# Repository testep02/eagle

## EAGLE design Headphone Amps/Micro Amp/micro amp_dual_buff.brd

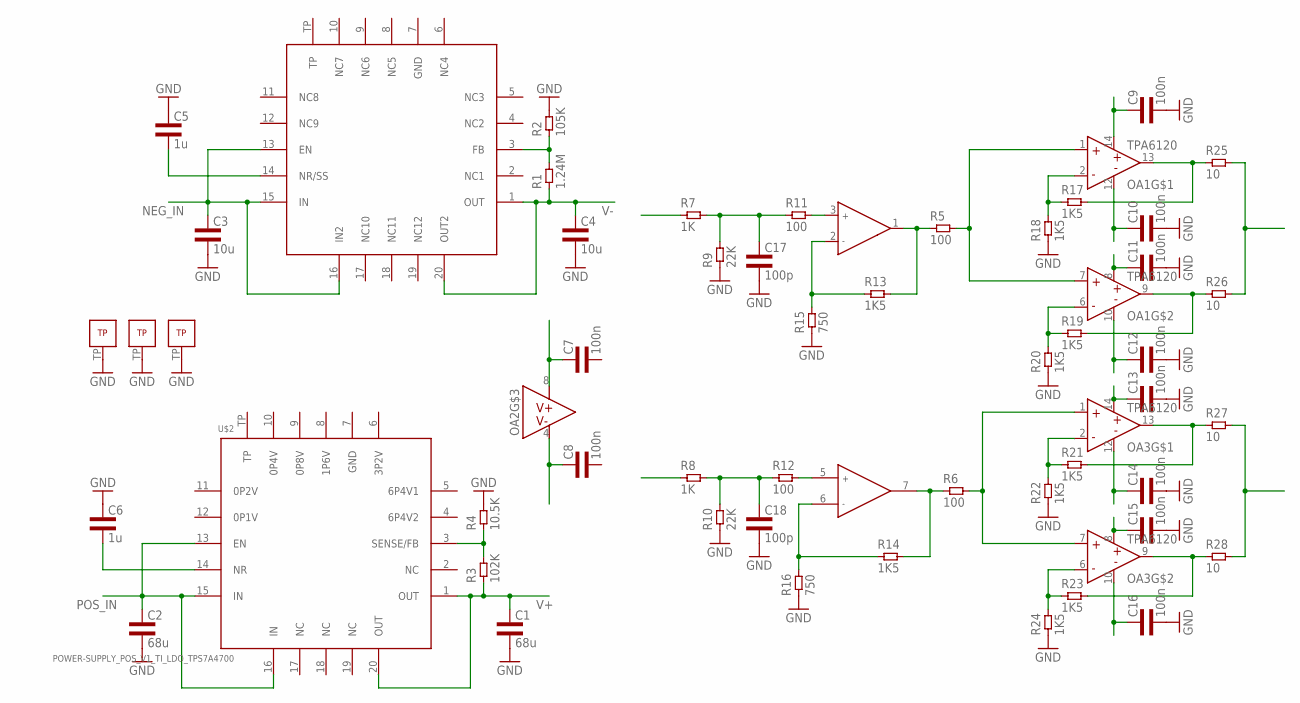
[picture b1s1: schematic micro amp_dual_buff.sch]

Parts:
C1, C2: 68u; 1210L3
C3, C4: 10u; 0805L3
C5, C6: 1u; 0603L3
C7, C8, C9, C10, C11, C12, C13, C14, C15, C16: 100n; 0402L3
C17, C18: 100p; 0402L3
OA1, OA3: TPA6120QFN; S-PVQFN-N14
OA2: OPA1612; S-PWSON-N8
R1: 1.24M; 0402L3
R2: 105K; 0402L3
R3: 102K; 0402L3
R4: 10.5K; 0402L3
R5, R6, R11, R12: 100; 0402L3
R7, R8: 1K; 0402L3
R9, R10: 22K; 0402L3
R13, R14, R17, R18, R19, R20, R21, R22, R23, R24: 1K5; 0402L3
R15, R16: 750; 0402L3
R25, R26, R27, R28: 10; 0805L3
U$1: POWER-SUPPLY_POS_V1_TI_LDO_TPS7A3301RGWT; POWER-SUPPLY_POS_V1_TI_LDO_VQFN-20
U$2: POWER-SUPPLY_POS_V1_TI_LDO_TPS7A4700; POWER-SUPPLY_POS_V1_TI_LDO_VQFN-20

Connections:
GND: C1.P$2 (2), C2.P$2 (2), C3.2, C4.2, C5.P$1 (1), C6.P$1 (1), C9.P$2 (2), C10.P$2 (2), C11.P$2 (2), C12.P$2 (2), C13.P$2 (2), C14.P$2 (2), C15.P$2 (2), C16.P$2 (2), C17.P$2 (2), C18.P$2 (2), OA1.TP, OA2.TP, OA3.TP, R2.P$2 (2), R4.P$2 (2), R9.P$1 (1), R10.P$1 (1), R15.P$1 (1), R16.P$1 (1), R18.P$1 (1), R20.P$1 (1), R22.P$1 (1), R24.P$1 (1)
IN_L: R7.P$1 (1)
IN_R: R8.P$1 (1)
unnamed: R3.P$2 (2), R4.P$1 (1), U$2.3 (SENSE/FB)
unnamed: R1.P$2 (2), R2.P$1 (1), U$1.3 (FB)
unnamed: C5.P$2 (2), U$1.14 (NR/SS)
unnamed: C6.P$2 (2), U$2.14 (NR)
unnamed: OA1.1 (IN+), OA1.7 (IN+), R5.P$2 (2)
unnamed: OA3.1 (IN+), OA3.7 (IN+), R6.P$2 (2)
unnamed: OA2.1 (OUTA), R5.P$1 (1), R13.P$2 (2)
unnamed: OA2.7 (OUTB), R6.P$1 (1), R14.P$2 (2)
unnamed: C18.P$1 (1), R8.P$2 (2), R10.P$2 (2), R12.P$1 (1)
unnamed: C17.P$1 (1), R7.P$2 (2), R9.P$2 (2), R11.P$1 (1)
unnamed: OA2.3 (INA+), R11.P$2 (2)
unnamed: OA2.5 (INB+), R12.P$2 (2)
unnamed: OA2.2 (INA-), R13.P$1 (1), R15.P$2 (2)
unnamed: OA2.6 (INB-), R14.P$1 (1), R16.P$2 (2)
unnamed: OA1.13 (OUT), R17.P$2 (2), R25.1
unnamed: OA1.9 (OUT), R19.P$2 (2), R26.1
unnamed: OA3.13 (OUT), R21.P$2 (2), R27.1
unnamed: OA3.9 (OUT), R23.P$2 (2), R28.1
unnamed: OA1.2 (IN-), R17.P$1 (1), R18.P$2 (2)
unnamed: OA1.6 (IN-), R19.P$1 (1), R20.P$2 (2)
unnamed: OA3.2 (IN-), R21.P$1 (1), R22.P$2 (2)
unnamed: OA3.6 (IN-), R23.P$1 (1), R24.P$2 (2)
NEG_IN: C3.1, U$1.13 (EN), U$1.15 (IN), U$1.16 (IN2)
OUT_L: R25.2, R26.2
OUT_R: R27.2, R28.2
POS_IN: C2.P$1 (1), U$2.13 (EN), U$2.15 (IN), U$2.16 (IN)
V+: C1.P$1 (1), C7.P$1 (1), C9.P$1 (1), C11.P$1 (1), C13.P$1 (1), C15.P$1 (1), OA1.8 (V+), OA1.14 (V+), OA2.8 (V+), OA3.8 (V+), OA3.14 (V+), R3.P$1 (1), U$2.1 (OUT), U$2.20 (OUT)
V-: C4.1, C8.P$1 (1), C10.P$1 (1), C12.P$1 (1), C14.P$1 (1), C16.P$1 (1), OA1.10 (V-), OA1.12 (V-), OA2.4 (V-), OA3.10 (V-), OA3.12 (V-), R1.P$1 (1), U$1.1 (OUT), U$1.20 (OUT2)

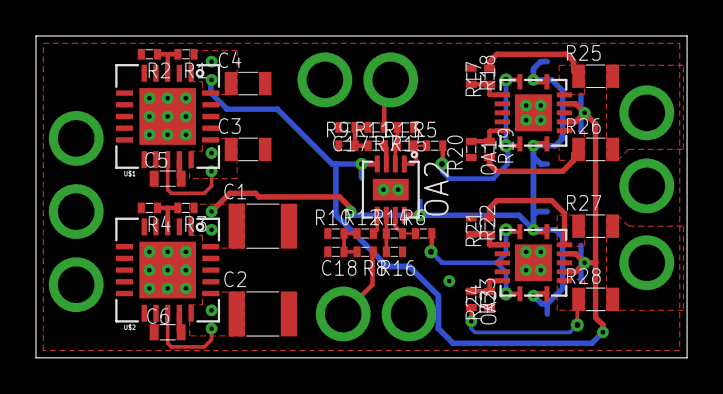
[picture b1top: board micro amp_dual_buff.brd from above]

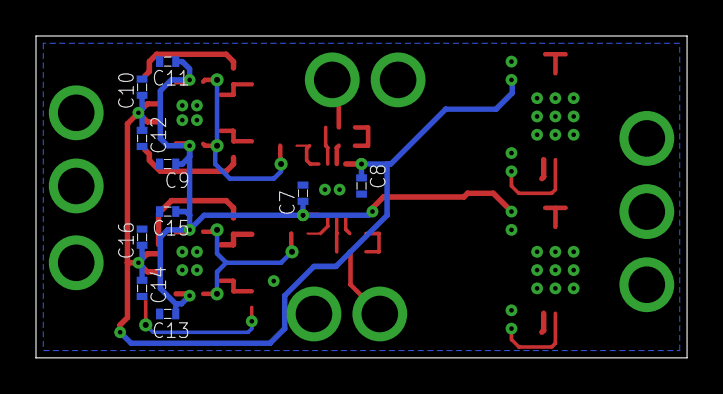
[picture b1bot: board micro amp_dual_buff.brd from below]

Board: 2 copper layers, 36.2 x 17.9 mm, 51 parts (10 on the bottom side), 29 nets.

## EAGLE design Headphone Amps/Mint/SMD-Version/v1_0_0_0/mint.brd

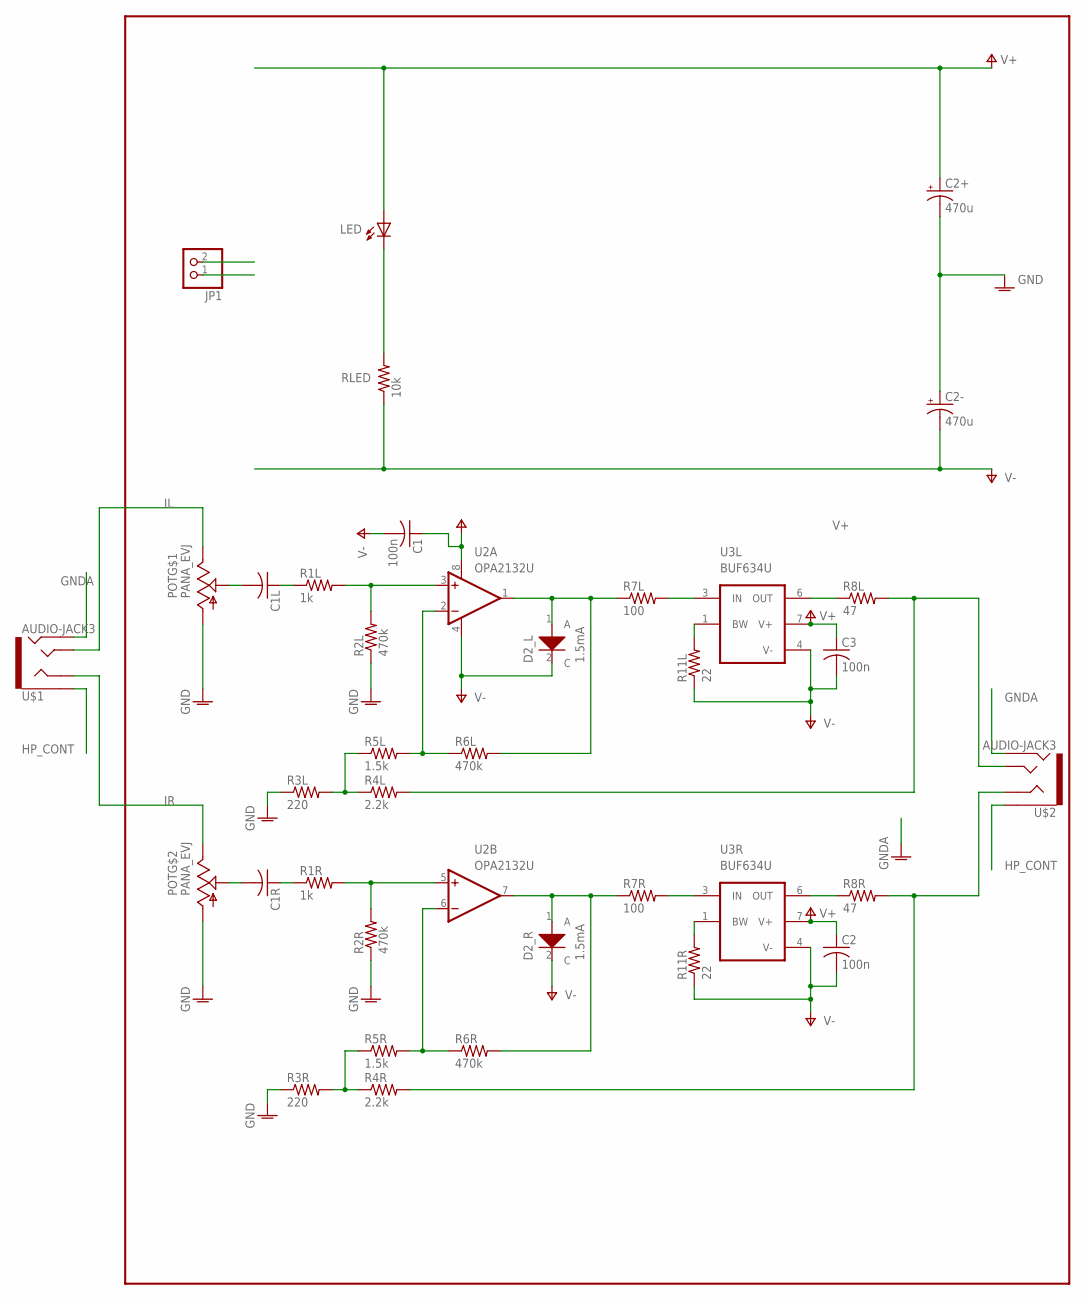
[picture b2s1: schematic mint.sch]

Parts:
C1, C2, C3: 100n; C0603
C1L, C1R: C-USC1210; C1210
C2+, C2-: 470u; PANASONIC_G
D2_L, D2_R: S-152T; SMD-2616
JP1: PINHD-1X2; 1X02
LED: LEDCHIP-LED0603; CHIP-LED0603
POT: PANA_EVJ; ALPS_RK27
R1L, R1R: 1k; R0603
R2L, R2R, R6L, R6R: 470k; R0603
R3L, R3R: 220; R0603
R4L, R4R: 2.2k; R0603
R5L, R5R: 1.5k; R0603
R7L, R7R: 100; R0603
R8L, R8R: 47; R0603
R11L, R11R: 22; R0603
RLED: 10k; R0603
U2: OPA2132U; SO08
U3L, U3R: BUF634U; SO08
U$1, U$2: AUDIO-JACK3; AUDIO-JACK-TRRS-SMD

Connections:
GNDA: C2+.-, C2-.+, POT.G1 (1), POT.G2 (1), R2L.1, R2R.1, R3L.1, R3R.1, U$1.RING2, U$2.RING2
HP_CONT: U$1.EARTH, U$2.EARTH
IL: POT.I1 (3), U$1.TIP
IR: POT.I2 (3), U$1.RING1
unnamed: C1L.1, R1L.1
unnamed: LED.C, RLED.2
unnamed: R1L.2, R2L.2, U2.3 (+IN)
unnamed: R8L.1, U3L.6 (OUT)
unnamed: D2_L.1 (A), R6L.2, R7L.1, U2.1 (OUT)
unnamed: R11L.2, U3L.1 (BW)
unnamed: R5L.2, R6L.1, U2.2 (-IN)
unnamed: R3L.2, R4L.1, R5L.1
unnamed: R7L.2, U3L.3 (IN)
unnamed: C1L.2, POT.O1 (2)
unnamed: C1R.1, R1R.1
unnamed: R1R.2, R2R.2, U2.5 (+IN)
unnamed: D2_R.1 (A), R6R.2, R7R.1, U2.7 (OUT)
unnamed: R8R.1, U3R.6 (OUT)
unnamed: R11R.2, U3R.1 (BW)
unnamed: R5R.2, R6R.1, U2.6 (-IN)
unnamed: R3R.2, R4R.1, R5R.1
unnamed: R7R.2, U3R.3 (IN)
unnamed: C1R.2, POT.O2 (2)
OL: R4L.2, R8L.2, U$2.TIP
OR: R4R.2, R8R.2, U$2.RING1
V+: C1.1, C2.1, C2+.+, C3.1, LED.A, U2.8 (V+), U3L.7 (V+), U3R.7 (V+)
V-: C1.2, C2.2, C2-.-, C3.2, D2_L.2 (C), D2_R.2 (C), R11L.1, R11R.1, RLED.1, U2.4 (V-), U3L.4 (V-), U3R.4 (V-)

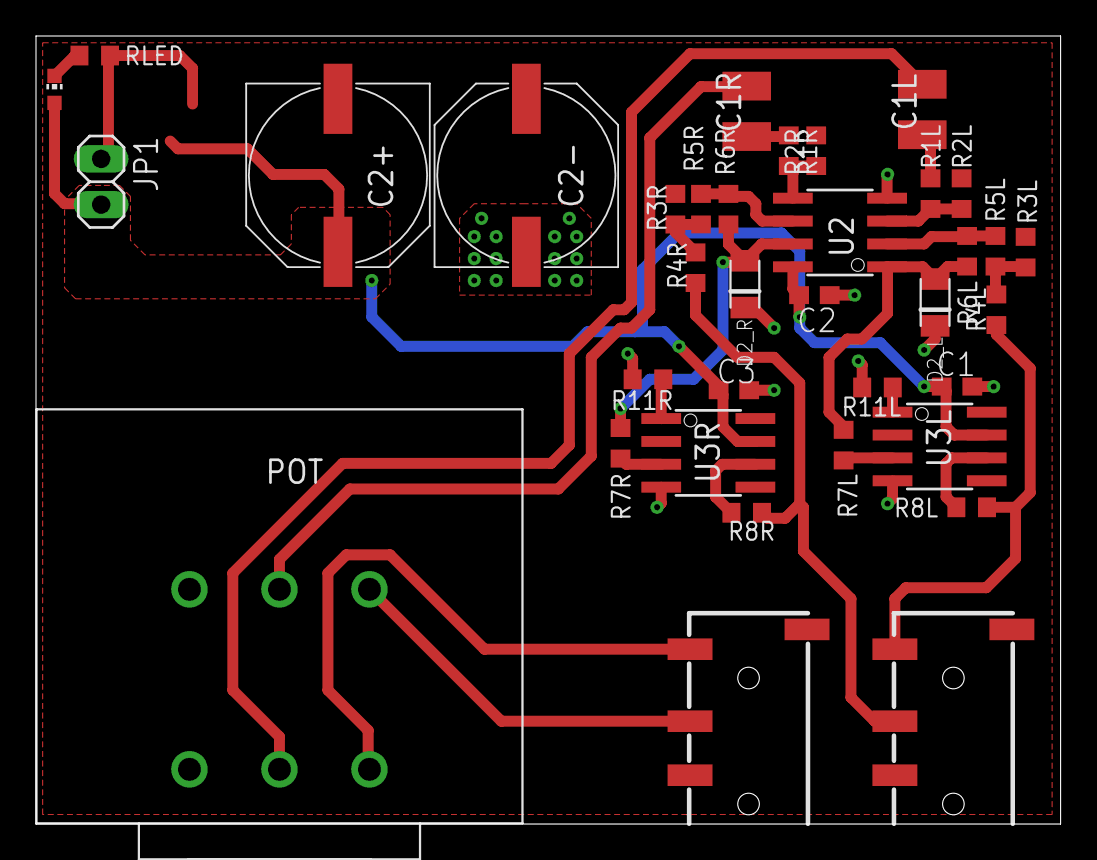
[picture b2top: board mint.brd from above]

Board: 2 copper layers, 56.9 x 43.8 mm, 36 parts (0 on the bottom side), 27 nets.

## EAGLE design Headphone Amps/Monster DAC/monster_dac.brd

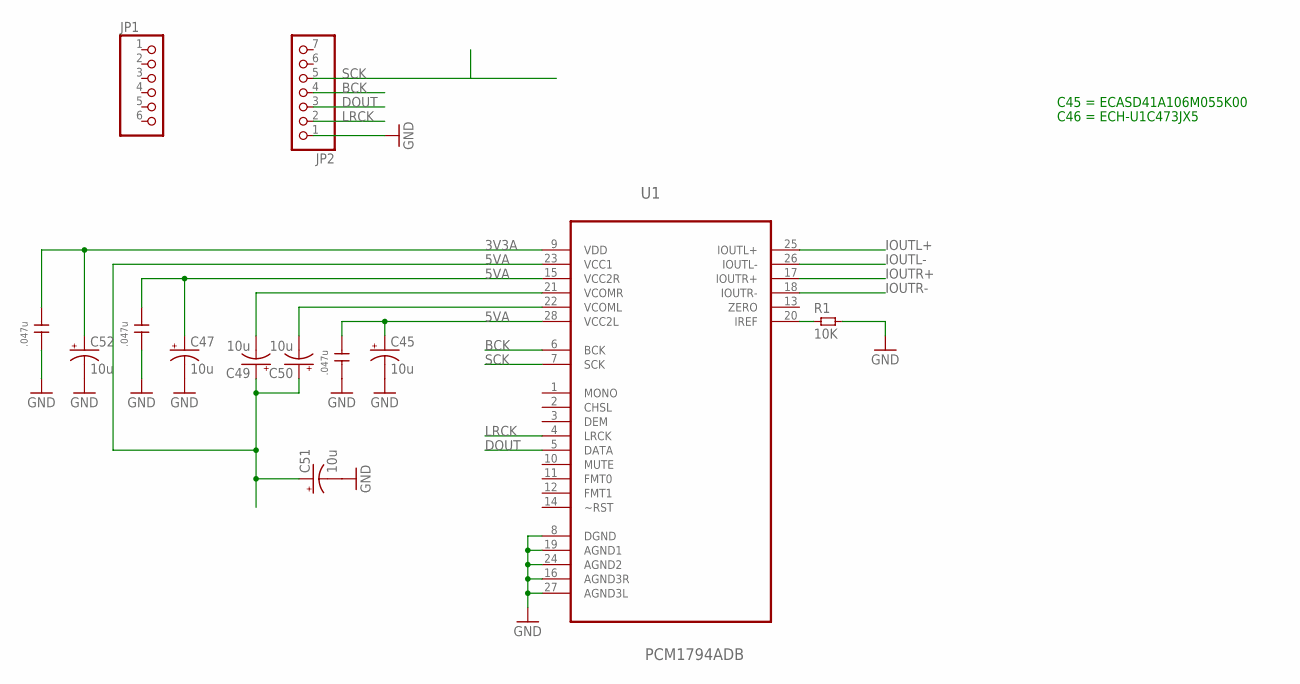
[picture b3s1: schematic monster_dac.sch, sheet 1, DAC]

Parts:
C45, C47, C49, C50, C51, C52: 10u; E2-5
C46, C48, C53: .047u; 2,5X6,5RM5,0
JP1: PINHD-1X6; 1X06
JP2: PINHD-1X7; 1X07
R1: 10K; 0603L3
U1: PCM1794ADB; SOP65P780X200-28N

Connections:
3V3A: C52.+, C53.1, U1.9 (VDD)
5VA: C45.+, C46.1, C47.+, C48.1, C49.+, C50.+, C51.+, U1.15 (VCC2R), U1.23 (VCC1), U1.28 (VCC2L)
BCK: JP2.4, U1.6 (BCK)
DOUT: JP2.3, U1.5 (DATA)
GND: C45.-, C46.2, C47.-, C48.2, C51.-, C52.-, C53.2, JP2.1, R1.P$2 (2), U1.8 (DGND), U1.16 (AGND3R), U1.19 (AGND1), U1.24 (AGND2), U1.27 (AGND3L); also elsewhere on the board
IOUTL+: U1.25 (IOUTL+); also elsewhere on the board
IOUTL-: U1.26 (IOUTL-); also elsewhere on the board
IOUTR+: U1.17 (IOUTR+); also elsewhere on the board
IOUTR-: U1.18 (IOUTR-); also elsewhere on the board
LRCK: JP2.2, U1.4 (LRCK)
unnamed: R1.P$1 (1), U1.20 (IREF)
unnamed: C50.-, U1.22 (VCOML)
unnamed: C49.-, U1.21 (VCOMR)
SCK: JP2.5, U1.7 (SCK)

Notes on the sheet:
C45 = ECASD41A106M055K00
C46 = ECH-U1C473JX5

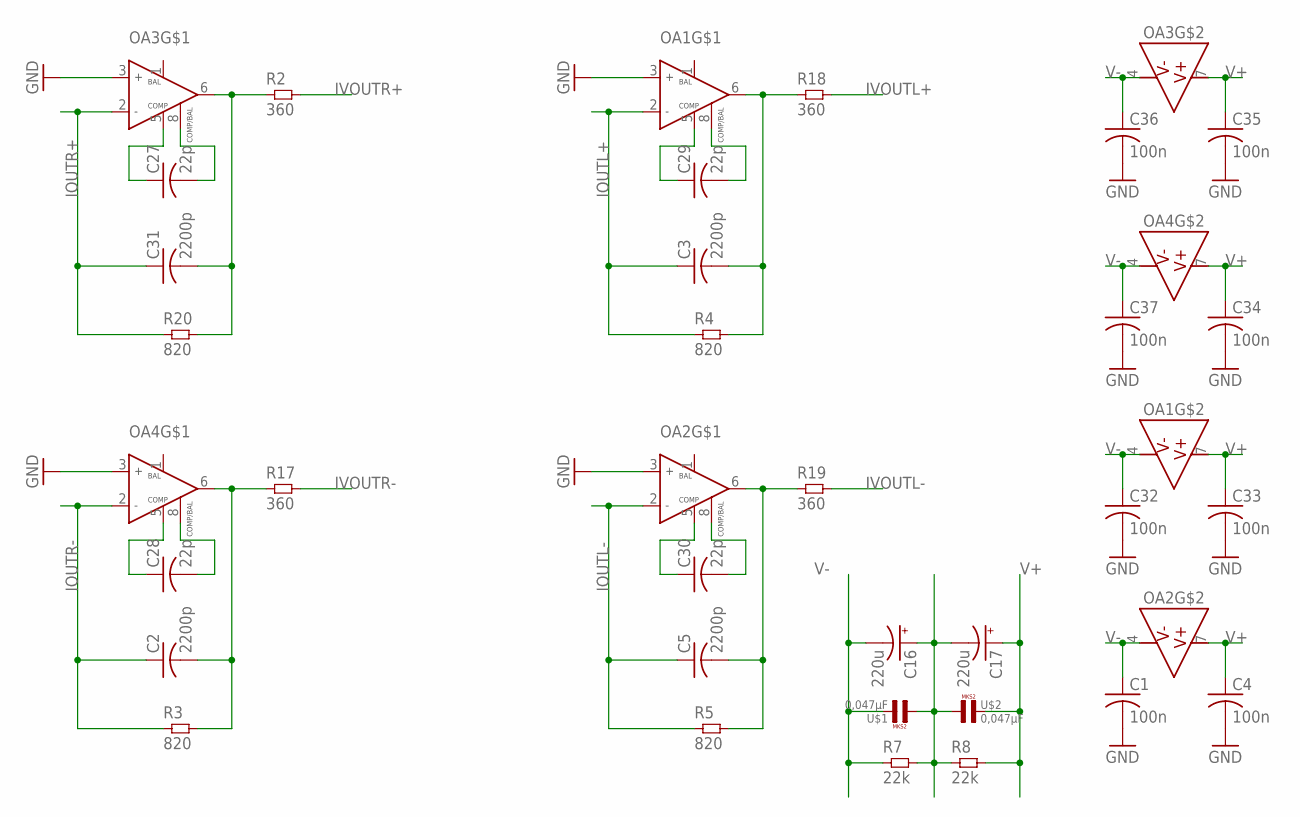
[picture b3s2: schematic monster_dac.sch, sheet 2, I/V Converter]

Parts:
C1, C4, C32, C33, C34, C35, C36, C37: 100n; C0603
C2, C3, C5, C31: 2200p; C0603
C16, C17: 220u; E2,5-6
C27, C28, C29, C30: 22p; C0603
OA1, OA2, OA3, OA4: NE5534ADSOIC8; SOIC-8
R2, R17, R18, R19: 360; 0603L3
R3, R4, R5, R20: 820; 0603L3
R7, R8: 22k; 0603L3
U$1, U$2: 0,047µF; R5B2K5

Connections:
GND: C1.2, C4.2, C16.+, C17.-, C32.2, C33.2, C34.2, C35.2, C36.2, C37.2, OA1.3 (IN+), OA2.3 (IN+), OA3.3 (IN+), OA4.3 (IN+), R7.P$2 (2), R8.P$1 (1), U$1.1, U$2.1; also elsewhere on the board
IOUTL+: C3.1, OA1.2 (IN-), R4.P$1 (1); also elsewhere on the board
IOUTL-: C5.1, OA2.2 (IN-), R5.P$1 (1); also elsewhere on the board
IOUTR+: C31.1, OA3.2 (IN-), R20.P$1 (1); also elsewhere on the board
IOUTR-: C2.1, OA4.2 (IN-), R3.P$1 (1); also elsewhere on the board
IVOUTL+: R18.P$2 (2); also elsewhere on the board
IVOUTL-: R19.P$2 (2); also elsewhere on the board
IVOUTR+: R2.P$2 (2); also elsewhere on the board
IVOUTR-: R17.P$2 (2); also elsewhere on the board
unnamed: C27.1, OA3.5 (COMP)
unnamed: C27.2, OA3.8 (COMP/BAL)
unnamed: C28.1, OA4.5 (COMP)
unnamed: C28.2, OA4.8 (COMP/BAL)
unnamed: C29.1, OA1.5 (COMP)
unnamed: C29.2, OA1.8 (COMP/BAL)
unnamed: C30.1, OA2.5 (COMP)
unnamed: C30.2, OA2.8 (COMP/BAL)
unnamed: C31.2, OA3.6 (OUT), R2.P$1 (1), R20.P$2 (2)
unnamed: C2.2, OA4.6 (OUT), R3.P$2 (2), R17.P$1 (1)
unnamed: C3.2, OA1.6 (OUT), R4.P$2 (2), R18.P$1 (1)
unnamed: C5.2, OA2.6 (OUT), R5.P$2 (2), R19.P$1 (1)
V+: C4.1, C17.+, C33.1, C34.1, C35.1, OA1.7 (V+), OA2.7 (V+), OA3.7 (V+), OA4.7 (V+), R8.P$2 (2), U$2.2; also elsewhere on the board
V-: C1.1, C16.-, C32.1, C36.1, C37.1, OA1.4 (V-), OA2.4 (V-), OA3.4 (V-), OA4.4 (V-), R7.P$1 (1), U$1.2; also elsewhere on the board

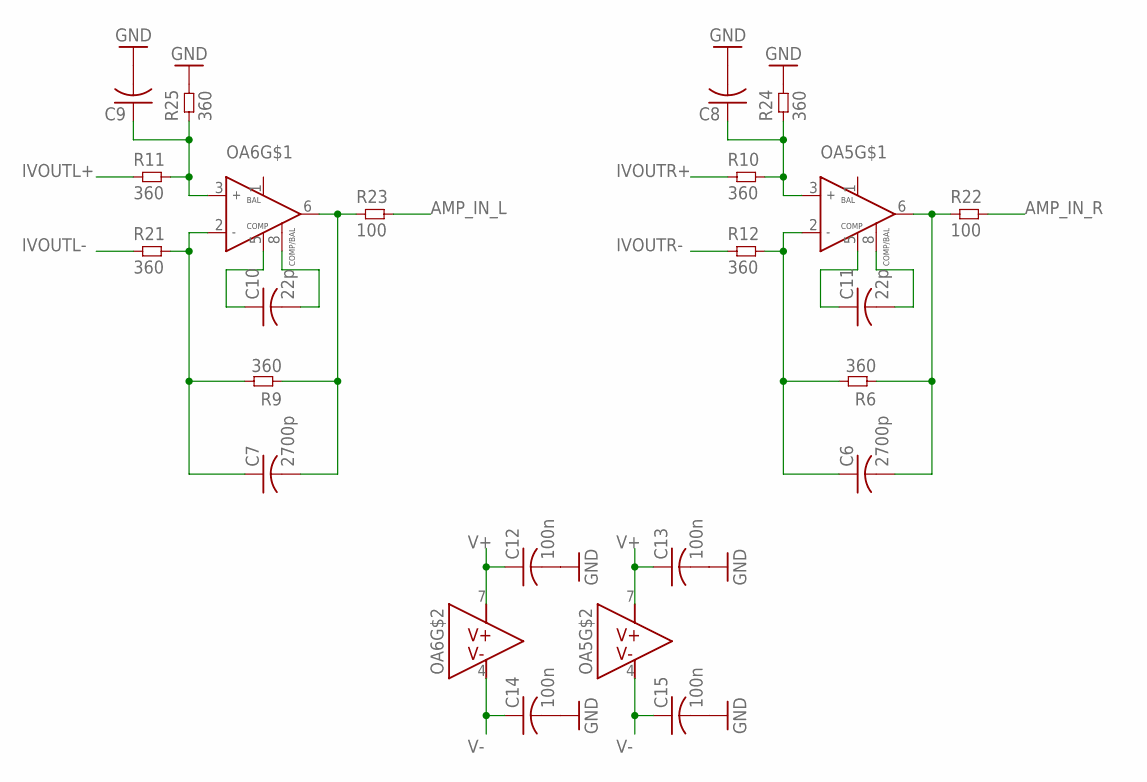
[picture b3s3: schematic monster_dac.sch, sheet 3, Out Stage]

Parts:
C6, C7: 2700p; C0603
C8, C9: C-USC0603; C0603
C10, C11: 22p; C0603
C12, C13, C14, C15: 100n; C0603
OA5, OA6: NE5534ADSOIC8; SOIC-8
R6, R9, R10, R11, R12, R21, R24, R25: 360; 0603L3
R22, R23: 100; 0603L3

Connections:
AMP_IN_L: R23.P$2 (2)
AMP_IN_R: R22.P$2 (2)
DIFF_L+: C9.1, OA6.3 (IN+), R11.P$2 (2), R25.P$1 (1)
DIFF_L-: C7.1, OA6.2 (IN-), R9.P$2 (2), R21.P$2 (2)
DIFF_OUT_L: C7.2, OA6.6 (OUT), R9.P$1 (1), R23.P$1 (1)
DIFF_OUT_R: C6.2, OA5.6 (OUT), R6.P$1 (1), R22.P$1 (1)
DIFF_R+: C8.1, OA5.3 (IN+), R10.P$2 (2), R24.P$1 (1)
DIFF_R-: C6.1, OA5.2 (IN-), R6.P$2 (2), R12.P$2 (2)
GND: C8.2, C9.2, C12.2, C13.2, C14.2, C15.2, R24.P$2 (2), R25.P$2 (2); also elsewhere on the board
IVOUTL+: R11.P$1 (1); also elsewhere on the board
IVOUTL-: R21.P$1 (1); also elsewhere on the board
IVOUTR+: R10.P$1 (1); also elsewhere on the board
IVOUTR-: R12.P$1 (1); also elsewhere on the board
unnamed: C10.1, OA6.5 (COMP)
unnamed: C10.2, OA6.8 (COMP/BAL)
unnamed: C11.1, OA5.5 (COMP)
unnamed: C11.2, OA5.8 (COMP/BAL)
V+: C12.1, C13.1, OA5.7 (V+), OA6.7 (V+); also elsewhere on the board
V-: C14.1, C15.1, OA5.4 (V-), OA6.4 (V-); also elsewhere on the board

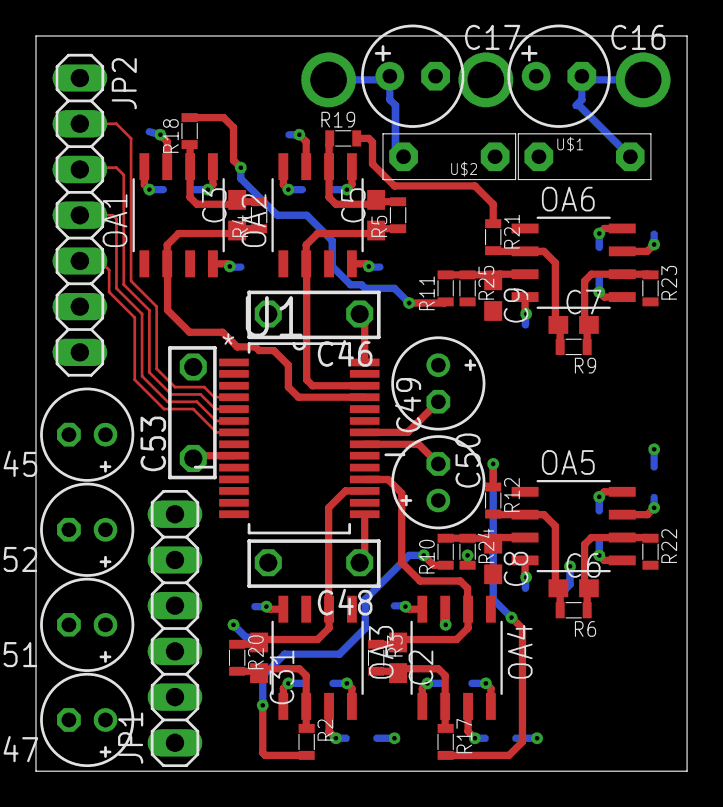
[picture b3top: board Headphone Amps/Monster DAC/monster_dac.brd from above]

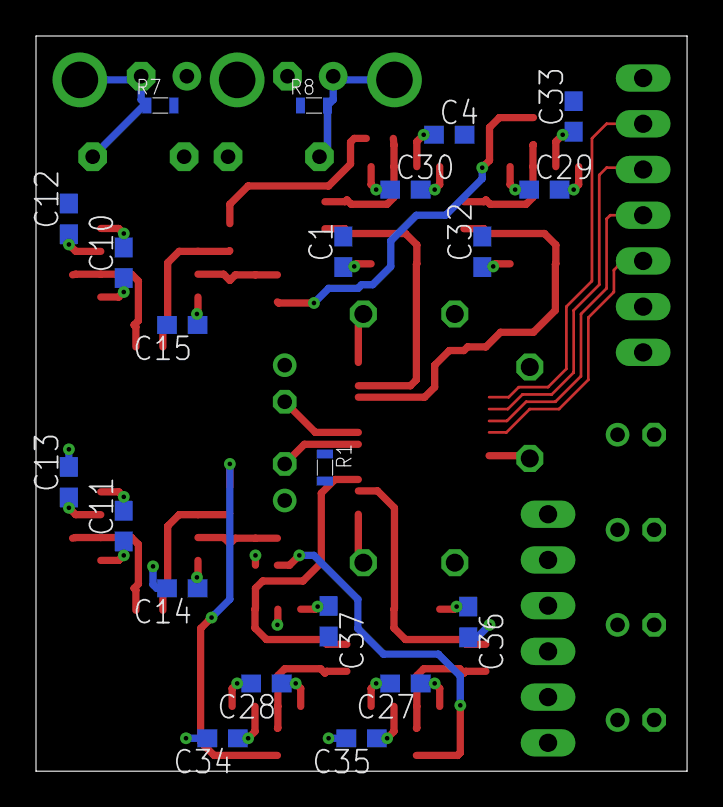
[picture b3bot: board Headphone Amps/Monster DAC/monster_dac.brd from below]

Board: 4 copper layers, 36.2 x 40.8 mm, 69 parts (21 on the bottom side), 42 nets.

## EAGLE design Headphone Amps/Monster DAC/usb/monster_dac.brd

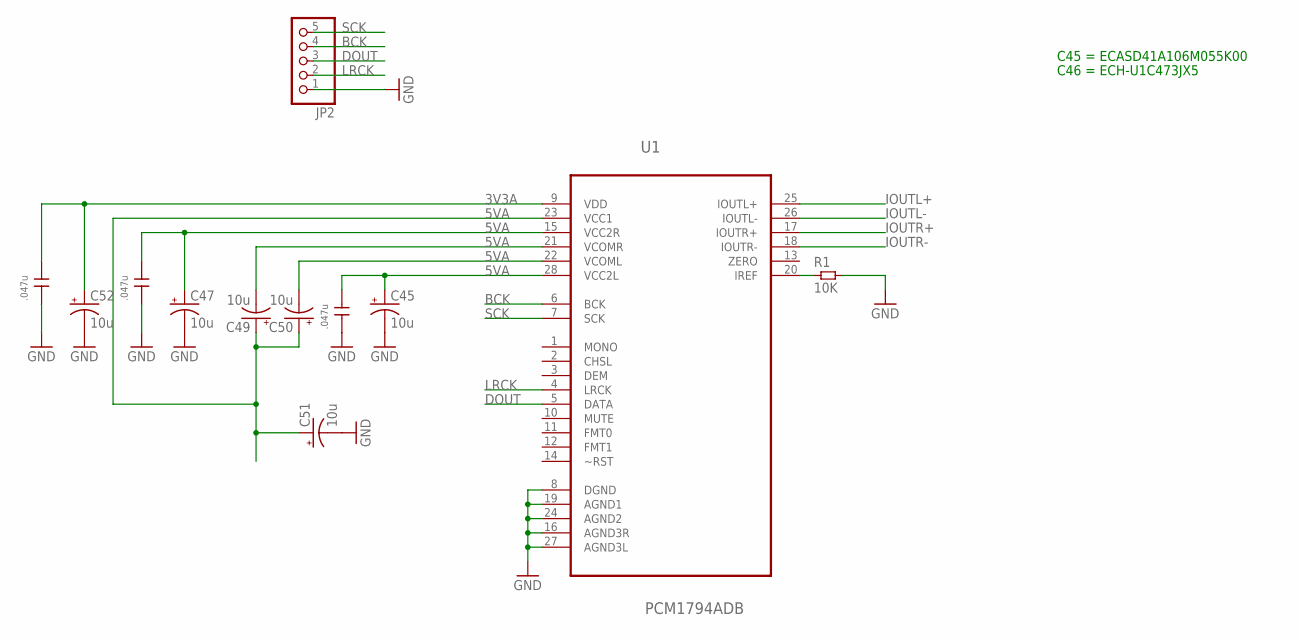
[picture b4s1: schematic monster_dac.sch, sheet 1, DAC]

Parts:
C45, C47, C49, C50, C51, C52: 10u; E2-5
C46, C48, C53: .047u; 2,5X6,5RM5,0
JP2: PINHD-1X5; 1X05
R1: 10K; 0603L3
U1: PCM1794ADB; SOP65P780X200-28N

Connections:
3V3A: C52.+, C53.1, U1.9 (VDD)
5VA: C45.+, C46.1, C47.+, C48.1, C49.+, C49.-, C50.+, C50.-, C51.+, U1.15 (VCC2R), U1.21 (VCOMR), U1.22 (VCOML), U1.23 (VCC1), U1.28 (VCC2L)
BCK: JP2.4, U1.6 (BCK)
DOUT: JP2.3, U1.5 (DATA)
GND: C45.-, C46.2, C47.-, C48.2, C51.-, C52.-, C53.2, JP2.1, R1.P$2 (2), U1.8 (DGND), U1.16 (AGND3R), U1.19 (AGND1), U1.24 (AGND2), U1.27 (AGND3L); also elsewhere on the board
IOUTL+: U1.25 (IOUTL+); also elsewhere on the board
IOUTL-: U1.26 (IOUTL-); also elsewhere on the board
IOUTR+: U1.17 (IOUTR+); also elsewhere on the board
IOUTR-: U1.18 (IOUTR-); also elsewhere on the board
LRCK: JP2.2, U1.4 (LRCK)
unnamed: R1.P$1 (1), U1.20 (IREF)
SCK: JP2.5, U1.7 (SCK)

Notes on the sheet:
C45 = ECASD41A106M055K00
C46 = ECH-U1C473JX5

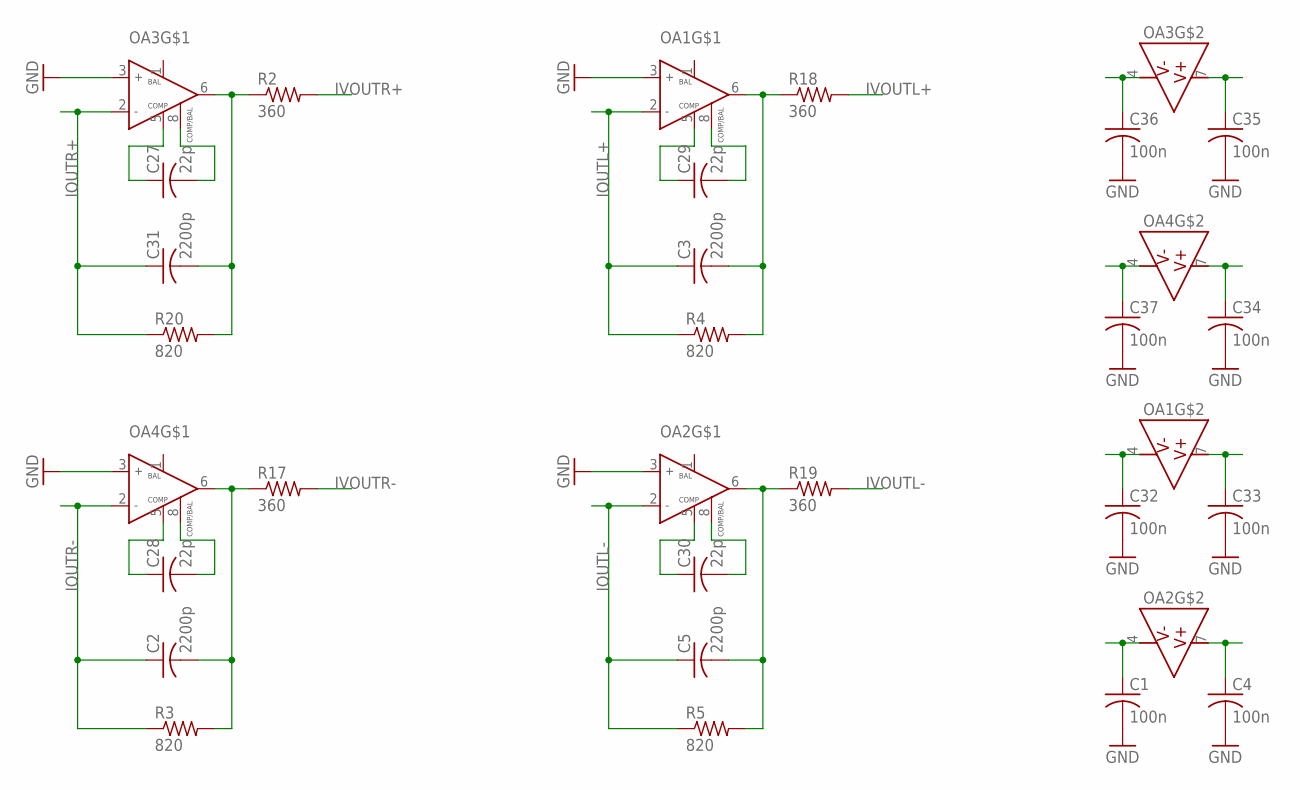
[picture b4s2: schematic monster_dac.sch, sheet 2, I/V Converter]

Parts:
C1, C4, C32, C33, C34, C35, C36, C37: 100n; C0603
C2, C3, C5, C31: 2200p; C0603
C27, C28, C29, C30: 22p; C0603
OA1, OA2, OA3, OA4: NE5534ADSOIC8; SOIC-8
R2, R17, R18, R19: 360; R0603
R3, R4, R5, R20: 820; R0603

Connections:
GND: C1.2, C4.2, C32.2, C33.2, C34.2, C35.2, C36.2, C37.2, OA1.3 (IN+), OA2.3 (IN+), OA3.3 (IN+), OA4.3 (IN+); also elsewhere on the board
IOUTL+: C3.1, OA1.2 (IN-), R4.1; also elsewhere on the board
IOUTL-: C5.1, OA2.2 (IN-), R5.1; also elsewhere on the board
IOUTR+: C31.1, OA3.2 (IN-), R20.1; also elsewhere on the board
IOUTR-: C2.1, OA4.2 (IN-), R3.1; also elsewhere on the board
IVOUTL+: R18.2; also elsewhere on the board
IVOUTL-: R19.2; also elsewhere on the board
IVOUTR+: R2.2; also elsewhere on the board
IVOUTR-: R17.2; also elsewhere on the board
unnamed: C4.1, OA2.7 (V+)
unnamed: C1.1, OA2.4 (V-)
unnamed: C33.1, OA1.7 (V+)
unnamed: C32.1, OA1.4 (V-)
unnamed: C27.1, OA3.5 (COMP)
unnamed: C27.2, OA3.8 (COMP/BAL)
unnamed: C28.1, OA4.5 (COMP)
unnamed: C28.2, OA4.8 (COMP/BAL)
unnamed: C29.1, OA1.5 (COMP)
unnamed: C29.2, OA1.8 (COMP/BAL)
unnamed: C30.1, OA2.5 (COMP)
unnamed: C30.2, OA2.8 (COMP/BAL)
unnamed: C31.2, OA3.6 (OUT), R2.1, R20.2
unnamed: C2.2, OA4.6 (OUT), R3.2, R17.1
unnamed: C3.2, OA1.6 (OUT), R4.2, R18.1
unnamed: C5.2, OA2.6 (OUT), R5.2, R19.1
unnamed: C37.1, OA4.4 (V-)
unnamed: C36.1, OA3.4 (V-)
unnamed: C35.1, OA3.7 (V+)
unnamed: C34.1, OA4.7 (V+)

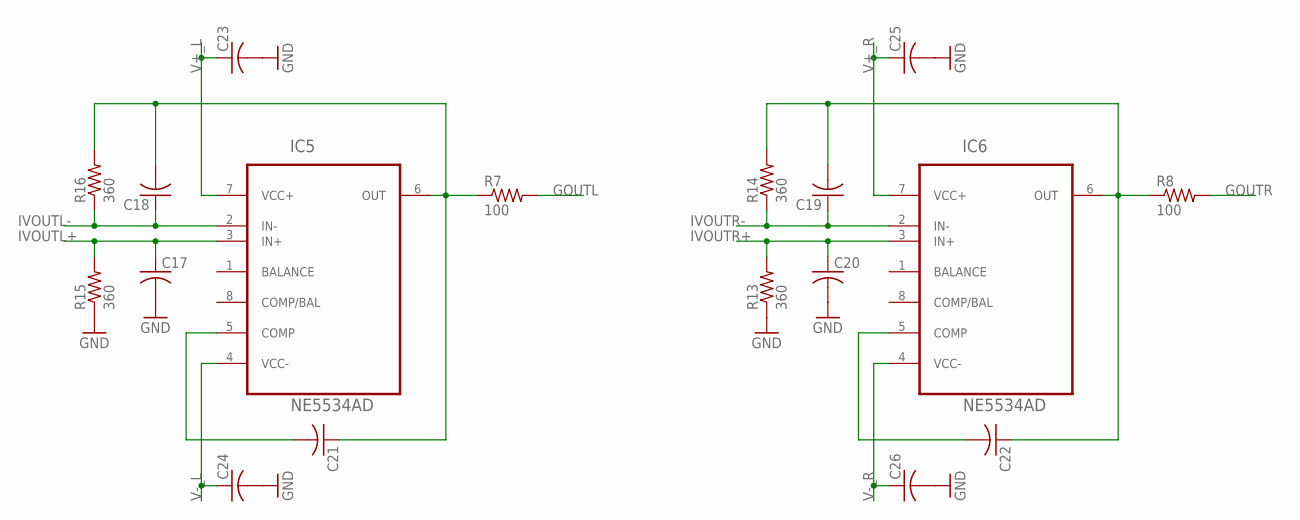
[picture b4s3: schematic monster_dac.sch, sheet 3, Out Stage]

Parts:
C17, C18, C19, C20, C21, C22, C23, C24, C25, C26: C-USC0603; C0603
IC5, IC6: NE5534AD; SOIC127P600X175-8N
R7, R8: 100; R0603
R13, R14, R15, R16: 360; R0603

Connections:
GND: C17.2, C20.2, C23.2, C24.2, C25.2, C26.2, R13.1, R15.1; also elsewhere on the board
GOUTL: R7.2
GOUTR: R8.2
IVOUTL+: C17.1, IC5.3 (IN+), R15.2; also elsewhere on the board
IVOUTL-: C18.1, IC5.2 (IN-), R16.1; also elsewhere on the board
IVOUTR+: C20.1, IC6.3 (IN+), R13.2; also elsewhere on the board
IVOUTR-: C19.1, IC6.2 (IN-), R14.1; also elsewhere on the board
unnamed: C18.2, C21.1, IC5.6 (OUT), R7.1, R16.2
unnamed: C19.2, C22.1, IC6.6 (OUT), R8.1, R14.2
unnamed: C21.2, IC5.5 (COMP)
unnamed: C22.2, IC6.5 (COMP)
V+_L: C23.1, IC5.7 (VCC+)
V+_R: C25.1, IC6.7 (VCC+)
V-_L: C24.1, IC5.4 (VCC-)
V-_R: C26.1, IC6.4 (VCC-)

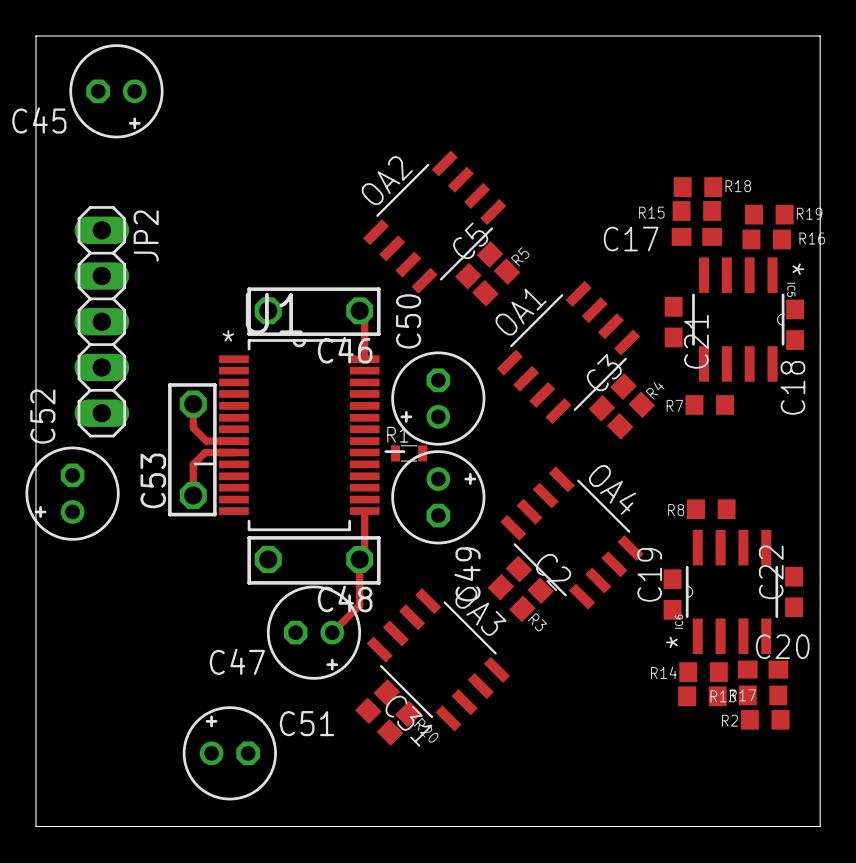
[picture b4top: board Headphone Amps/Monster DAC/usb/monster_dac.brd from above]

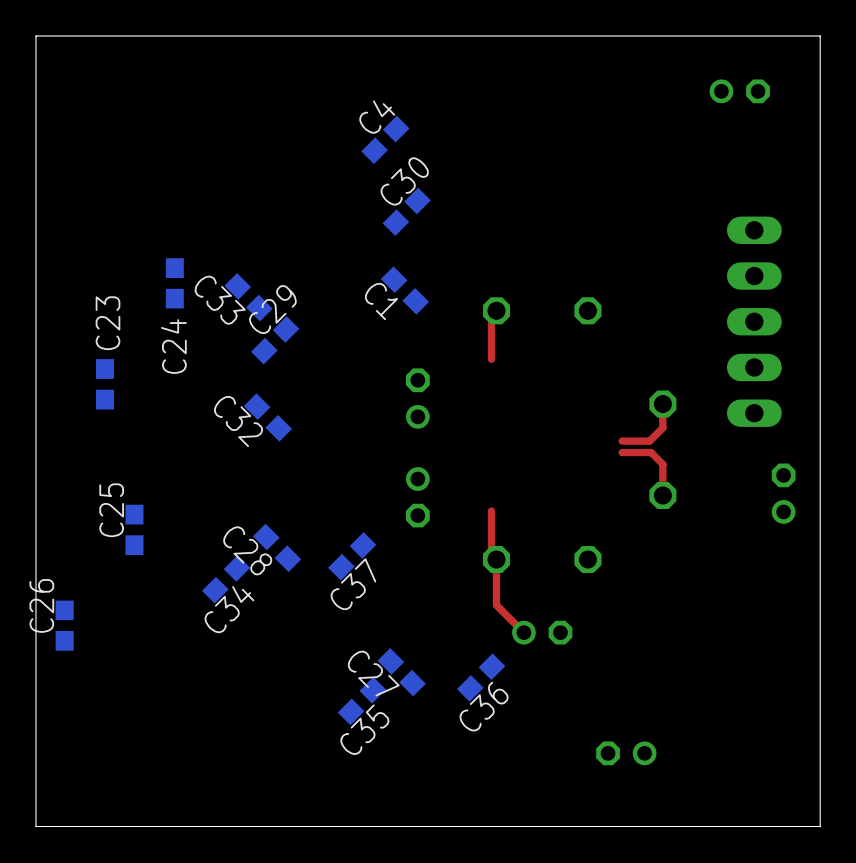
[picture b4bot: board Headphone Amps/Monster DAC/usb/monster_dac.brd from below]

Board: 4 copper layers, 43.6 x 43.9 mm, 58 parts (16 on the bottom side), 44 nets.

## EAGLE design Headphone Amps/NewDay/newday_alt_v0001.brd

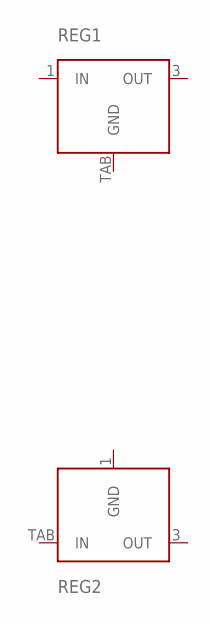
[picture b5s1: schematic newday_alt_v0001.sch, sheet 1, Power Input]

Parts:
REG1: MC7812; D2PAK
REG2: MC7912; D2PAK

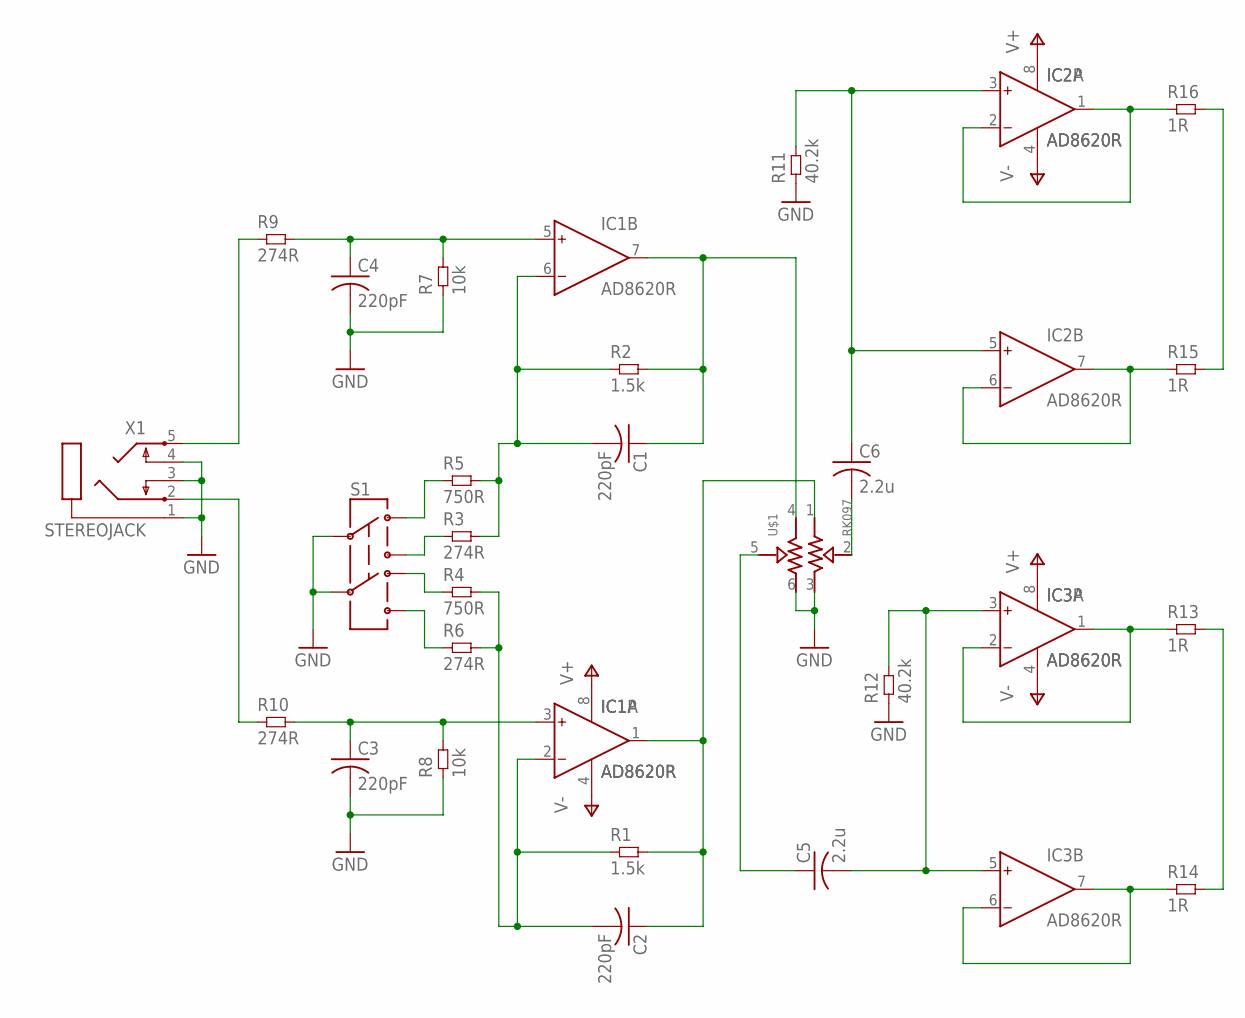
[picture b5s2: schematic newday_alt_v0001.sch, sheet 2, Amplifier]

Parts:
C1, C2, C3, C4: 220pF; C025-040X050
C5, C6: 2.2u; C050-075X075
IC1, IC2, IC3: AD8620R; SO8
R1, R2: 1.5k; 0603L3
R3, R6, R9, R10: 274R; 0603L3
R4, R5: 750R; 0603L3
R7, R8: 10k; 0603L3
R11, R12: 40.2k; 0603L3
R13, R14, R15, R16: 1R; 1210L3
S1: SWITCH-DPDTOS; OS
U$1: RK097
X1: STEREOJACK; STX3100

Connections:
GND: C3.2, C4.2, R7.P$1 (1), R8.P$1 (1), R11.P$1 (1), R12.P$1 (1), S1.2, S1.5, U$1.3, U$1.6, X1.1, X1.3, X1.4
unnamed: C1.1, IC1.7 (OUT), R2.P$2 (2), U$1.4
unnamed: C2.1, IC1.1 (OUT), R1.P$2 (2), U$1.1
unnamed: C1.2, IC1.6 (IN-), R2.P$1 (1), R3.P$2 (2), R5.P$2 (2)
unnamed: C2.2, IC1.2 (IN-), R1.P$1 (1), R4.P$2 (2), R6.P$2 (2)
unnamed: R5.P$1 (1), S1.1
unnamed: R3.P$1 (1), S1.3
unnamed: R6.P$1 (1), S1.6
unnamed: R4.P$1 (1), S1.4
unnamed: C6.2, U$1.2
unnamed: C6.1, IC2.3 (IN+), IC2.5 (IN+), R11.P$2 (2)
unnamed: C5.1, U$1.5
unnamed: C4.1, IC1.5 (IN+), R7.P$2 (2), R9.P$2 (2)
unnamed: C3.1, IC1.3 (IN+), R8.P$2 (2), R10.P$2 (2)
unnamed: C5.2, IC3.3 (IN+), IC3.5 (IN+), R12.P$2 (2)
unnamed: IC2.6 (IN-), IC2.7 (OUT), R15.P$1 (1)
unnamed: IC2.1 (OUT), IC2.2 (IN-), R16.P$1 (1)
unnamed: IC3.1 (OUT), IC3.2 (IN-), R13.P$1 (1)
unnamed: IC3.6 (IN-), IC3.7 (OUT), R14.P$1 (1)
unnamed: R15.P$2 (2), R16.P$2 (2)
unnamed: R13.P$2 (2), R14.P$2 (2)
unnamed: R9.P$1 (1), X1.5
unnamed: R10.P$1 (1), X1.2
V+: IC1.8 (V+), IC2.8 (V+), IC3.8 (V+)
V-: IC1.4 (V-), IC2.4 (V-), IC3.4 (V-)

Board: 2 copper layers, 30 parts (0 on the bottom side), 25 nets, no tracks yet.

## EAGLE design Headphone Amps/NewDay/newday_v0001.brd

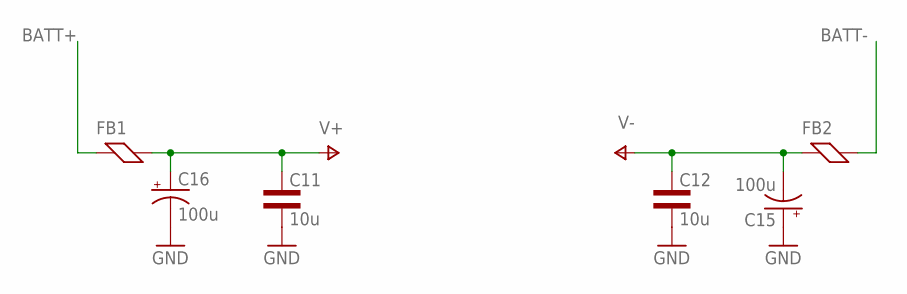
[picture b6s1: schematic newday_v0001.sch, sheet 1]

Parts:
C11, C12: 10u; 1210L3
C15, C16: 100u; E5-10,5
FB1, FB2: FERRITE0805L3; 0805L3

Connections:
BATT+: FB1.1
BATT-: FB2.2
GND: C11.P$2 (2), C12.P$2 (2), C15.+, C16.-; also elsewhere on the board
V+: C11.P$1 (1), C16.+, FB1.2; also elsewhere on the board
V-: C12.P$1 (1), C15.-, FB2.1; also elsewhere on the board

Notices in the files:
parts and their libraries:
SparkFun-Aesthetics: Licensing: CC v3.0 Share-Alike You are welcome to use this library for commercial purposes.
